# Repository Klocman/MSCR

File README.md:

## MSCR
MSCR is a three-axis DC motor controller for use with robotic arms, for example camera cranes. It can work with any potentiometer-based joystick, and can record and replay movements. This project contains the board layout and firmware. 

## Compiling / Software required
Boards and schematics were created with Eagle PCB v6.6.0. 

Firmare can be opened and compiled with Atmel Studio 6 or newer.

## Photos of the finished controller
[You can view the full gallery here](https://github.com/Klocman/MSCR/tree/master/Documentation/Photos)

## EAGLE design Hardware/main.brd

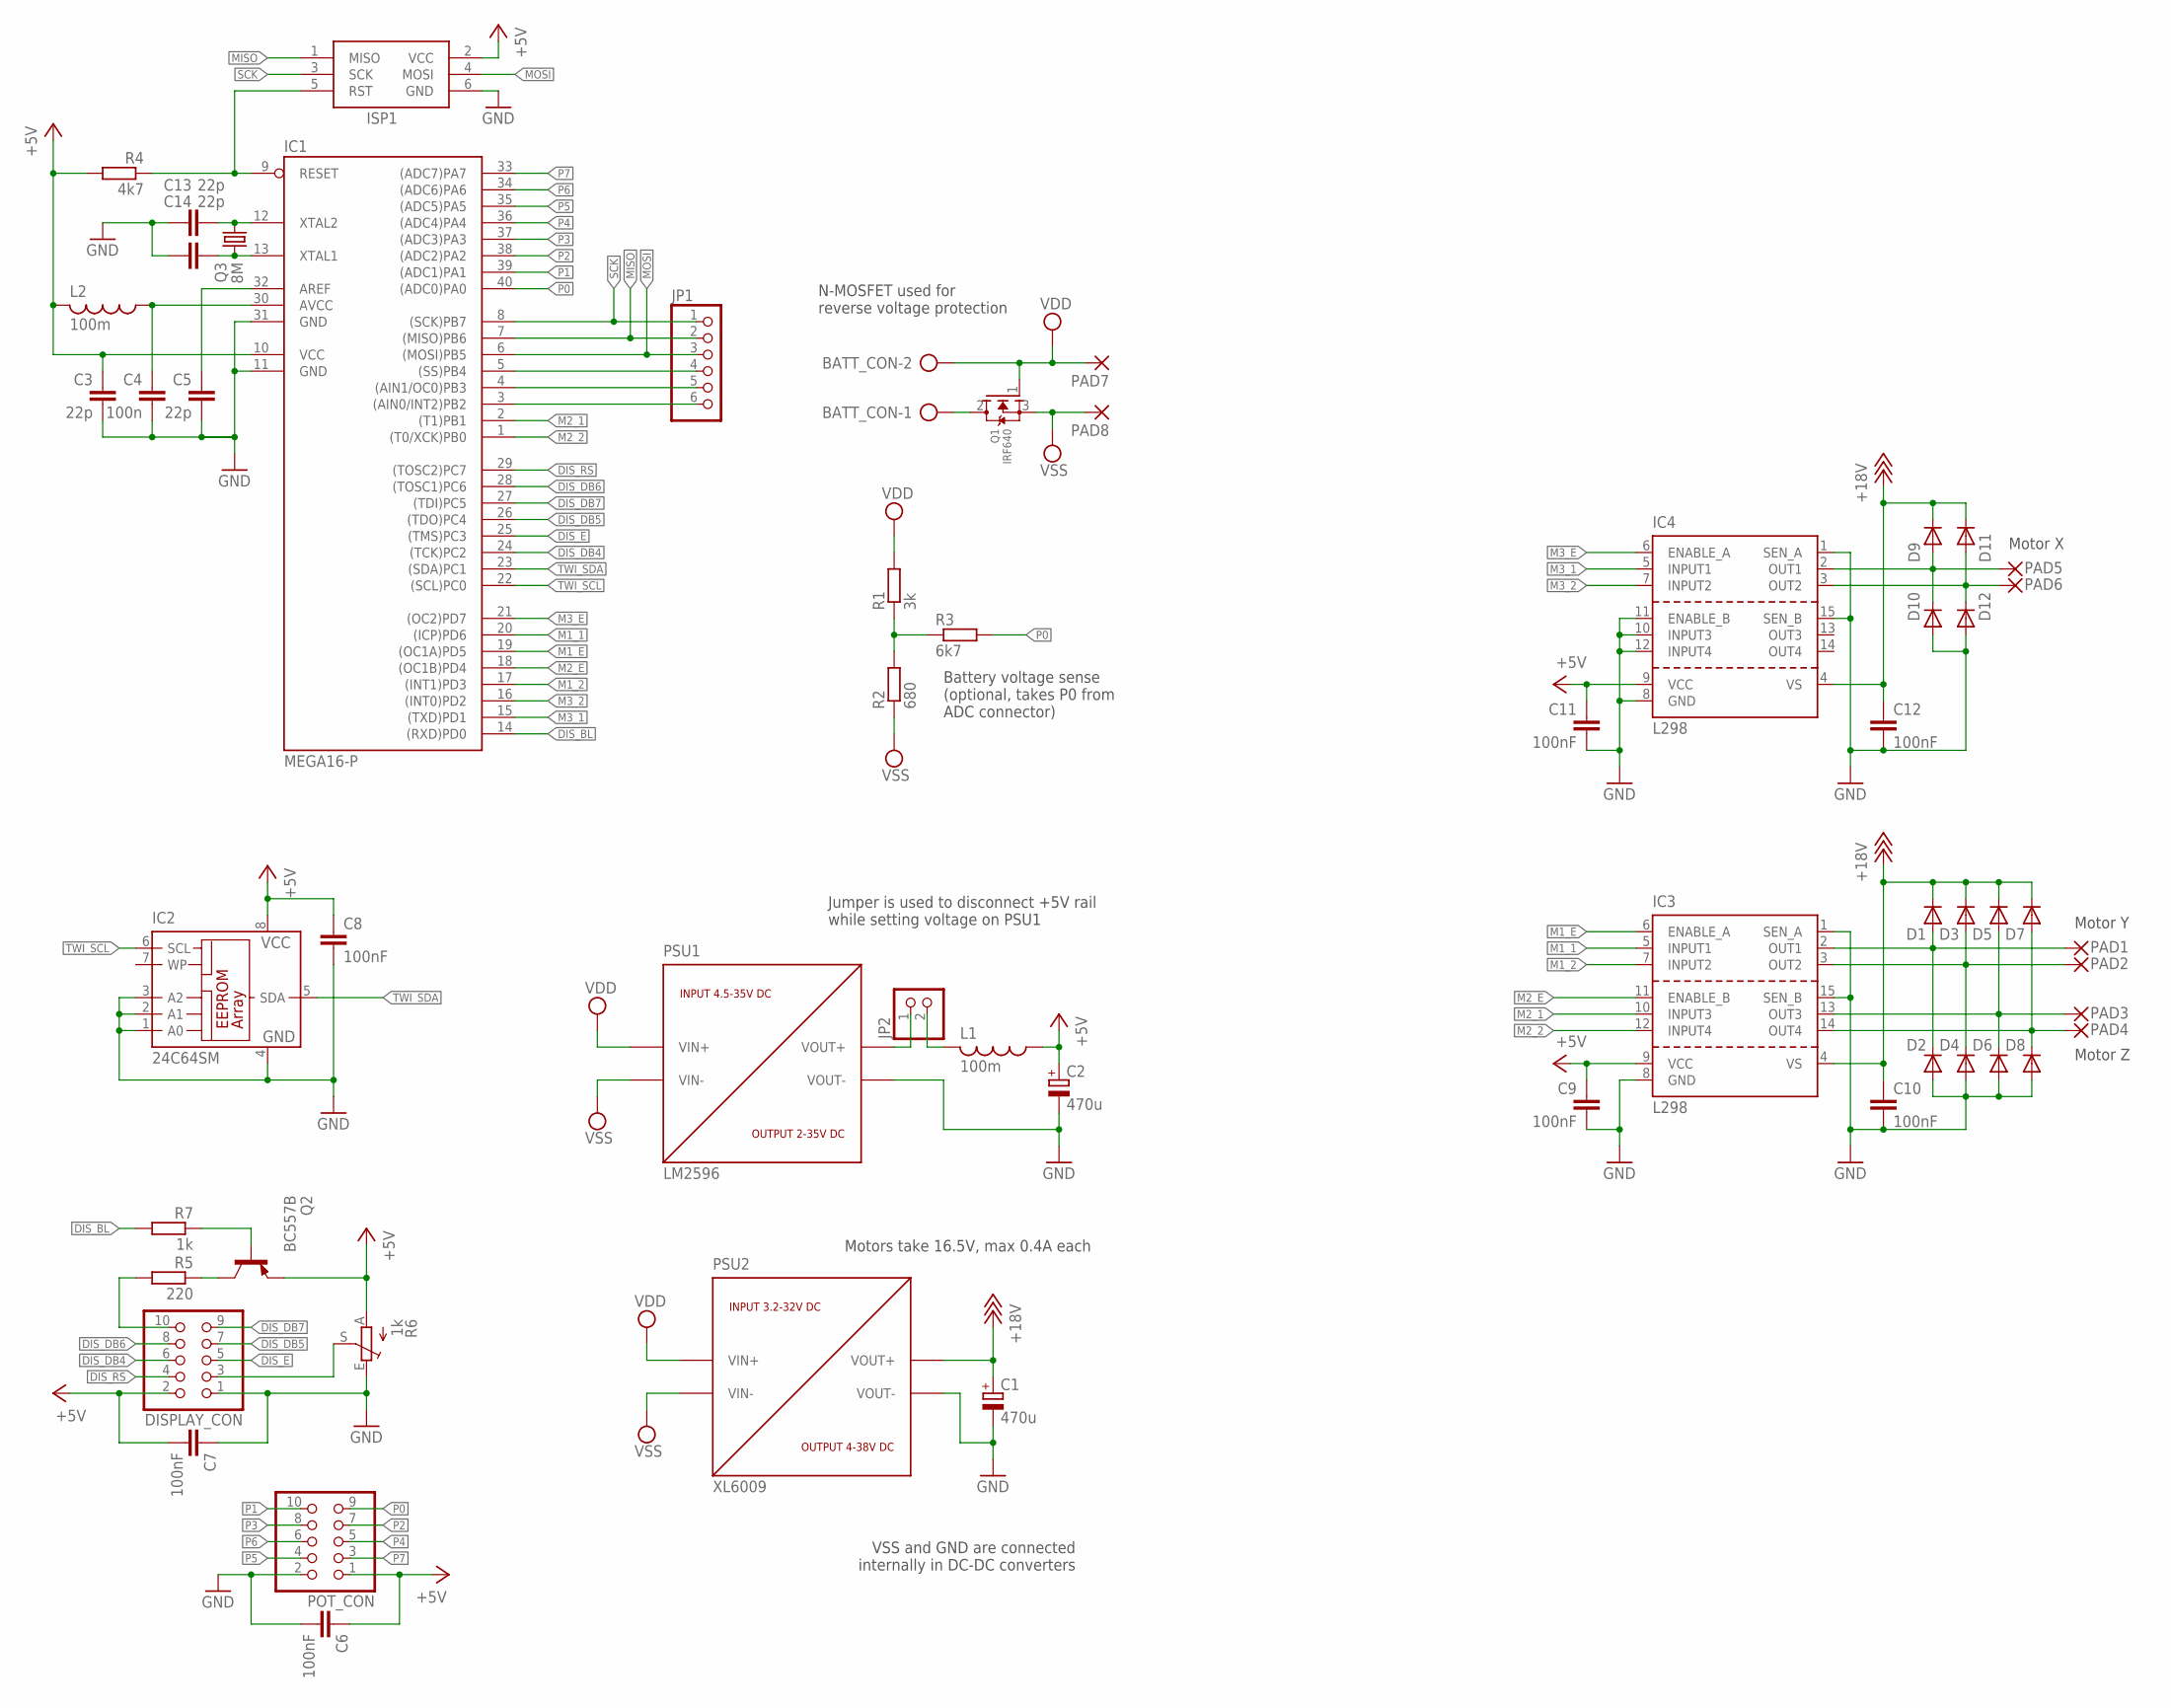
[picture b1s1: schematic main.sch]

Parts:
BATT_CON: AK500/2-H
C1: 470u; E3,5-8
C2: 470u; E5-8,5
C3, C5, C13, C14: 22p; C025-025X050
C4: 100n; C025-025X050
C6: 100nF; C025-025X050
C7, C8: 100nF; C050-024X044
C9, C10, C11, C12: 100nF; C075-032X103
D1, D2, D3, D4, D5, D6, D7, D8, D9, D10, D11, D12: UF4003; DO41-10
DISPLAY_CON: PINHD-2X5; 2X05
IC1: MEGA16-P; DIL40
IC2: 24C64SM; SO-08M
IC3, IC4: L298; MULTIWATT-15
ISP1: AVRISP-6; AVRISP
JP1: PINHD-1X6; 1X06
JP2: PINHD-1X2; 1X02
L1, L2: 100m; 0204/7
PAD1, PAD2, PAD3, PAD4, PAD5, PAD6, PAD7, PAD8: 2,54/1,1KLOCWIRE1; KLOCWIRE1
POT_CON: PINHD-2X5; 2X05
PSU1: LM2596; DC-DC_CONV_MODULE
PSU2: XL6009; DC-DC_CONV_MODULE
Q1: IRF640; TO220V
Q2: BC557B; TO92-EBC
Q3: 8M; TC26V
R1: 3k; 0204/7
R2: 680; 0204/7
R3: 6k7; 0204/5
R4: 4k7; 0204/5
R5: 220; 0204/7
R6: 1k; CA6V
R7: 1k; 0204/7

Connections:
+5V: C2.+, C3.1, C6.1, C7.2, C8.1, C9.1, C11.1, DISPLAY_CON.2, IC1.10 (VCC), IC2.8 (VCC), IC3.9 (VCC), IC4.9 (VCC), ISP1.2 (VCC), L1.1, L2.2, POT_CON.1, Q2.E, R4.2, R6.A
+18V: C1.+, C10.1, C12.1, D1.C, D3.C, D5.C, D7.C, D9.C, D11.C, IC3.4 (VS), IC4.4 (VS), PSU2.OUT+ (VOUT+)
DIS_BL: IC1.14 ((RXD)PD0), R7.2
DIS_DB4: DISPLAY_CON.6, IC1.24 ((TCK)PC2)
DIS_DB5: DISPLAY_CON.7, IC1.26 ((TDO)PC4)
DIS_DB6: DISPLAY_CON.8, IC1.28 ((TOSC1)PC6)
DIS_DB7: DISPLAY_CON.9, IC1.27 ((TDI)PC5)
DIS_E: DISPLAY_CON.5, IC1.25 ((TMS)PC3)
DIS_RS: DISPLAY_CON.4, IC1.29 ((TOSC2)PC7)
DIS_VO: DISPLAY_CON.3, R6.S
GND: C1.-, C2.-, C3.2, C4.2, C5.2, C6.2, C7.1, C8.2, C9.2, C10.2, C11.2, C12.2, C13.2, C14.2, D2.A, D4.A, D6.A, D8.A, D10.A, D12.A, DISPLAY_CON.1, IC1.11 (GND), IC1.31 (GND), IC2.1 (A0), IC2.2 (A1), IC2.3 (A2), IC2.4 (GND), IC3.1 (SEN_A), IC3.8 (GND), IC3.15 (SEN_B), IC4.1 (SEN_A), IC4.8 (GND), IC4.10 (INPUT3), IC4.11 (ENABLE_B), IC4.12 (INPUT4), IC4.15 (SEN_B), ISP1.6 (GND), POT_CON.2, PSU1.OUT- (VOUT-), PSU2.OUT- (VOUT-), R6.E
M1_1: IC1.20 ((ICP)PD6), IC3.5 (INPUT1)
M1_2: IC1.17 ((INT1)PD3), IC3.7 (INPUT2)
M1_E: IC1.19 ((OC1A)PD5), IC3.6 (ENABLE_A)
M2_1: IC1.2 ((T1)PB1), IC3.10 (INPUT3)
M2_2: IC1.1 ((T0/XCK)PB0), IC3.12 (INPUT4)
M2_E: IC1.18 ((OC1B)PD4), IC3.11 (ENABLE_B)
M3_1: IC1.15 ((TXD)PD1), IC4.5 (INPUT1)
M3_2: IC1.16 ((INT0)PD2), IC4.7 (INPUT2)
M3_E: IC1.21 ((OC2)PD7), IC4.6 (ENABLE_A)
MISO: IC1.7 ((MISO)PB6), ISP1.1 (MISO), JP1.2
MOSI: IC1.6 ((MOSI)PB5), ISP1.4 (MOSI), JP1.3
unnamed: JP2.1, PSU1.OUT+ (VOUT+)
unnamed: DISPLAY_CON.10, R5.2
unnamed: IC1.5 ((SS)PB4), JP1.4
unnamed: IC1.4 ((AIN1/OC0)PB3), JP1.5
unnamed: IC1.3 ((AIN0/INT2)PB2), JP1.6
unnamed: BATT_CON.1, Q1.2 (D)
unnamed: D1.A, D2.C, IC3.2 (OUT1), PAD1.1
unnamed: D3.A, D4.C, IC3.3 (OUT2), PAD2.1
unnamed: D5.A, D6.C, IC3.13 (OUT3), PAD3.1
unnamed: D9.A, D10.C, IC4.2 (OUT1), PAD5.1
unnamed: D7.A, D8.C, IC3.14 (OUT4), PAD4.1
unnamed: D11.A, D12.C, IC4.3 (OUT2), PAD6.1
unnamed: C13.1, IC1.12 (XTAL2), Q3.2
unnamed: Q2.C, R5.1
unnamed: C14.1, IC1.13 (XTAL1), Q3.1
unnamed: JP2.2, L1.2
unnamed: Q2.B, R7.1
unnamed: C4.1, IC1.30 (AVCC), L2.1
unnamed: C5.1, IC1.32 (AREF)
unnamed: R1.1, R2.2, R3.1
unnamed: IC1.9 (RESET), ISP1.5 (RST), R4.1
P0: IC1.40 ((ADC0)PA0), POT_CON.9, R3.2
P1: IC1.39 ((ADC1)PA1), POT_CON.10
P2: IC1.38 ((ADC2)PA2), POT_CON.7
P3: IC1.37 ((ADC3)PA3), POT_CON.8
P4: IC1.36 ((ADC4)PA4), POT_CON.5
P5: IC1.35 ((ADC5)PA5), POT_CON.4
P6: IC1.34 ((ADC6)PA6), POT_CON.6
P7: IC1.33 ((ADC7)PA7), POT_CON.3
SCK: IC1.8 ((SCK)PB7), ISP1.3 (SCK), JP1.1
TWI_SCL: IC1.22 ((SCL)PC0), IC2.6 (SCL)
TWI_SDA: IC1.23 ((SDA)PC1), IC2.5 (SDA)
VDD: BATT_CON.2, PAD7.1, PSU1.IN+ (VIN+), PSU2.IN+ (VIN+), Q1.1 (G), R1.2
VSS: PAD8.1, PSU1.IN- (VIN-), PSU2.IN- (VIN-), Q1.3 (S), R2.1

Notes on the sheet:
Battery voltage sense (optional, takes P0 from ADC connector)
VSS and GND are connected internally in DC-DC converters
Motors take 16.5V, max 0.4A each
N-MOSFET used for reverse voltage protection
Jumper is used to disconnect +5V rail while setting voltage on PSU1
Motor Y
Motor Z
Motor X

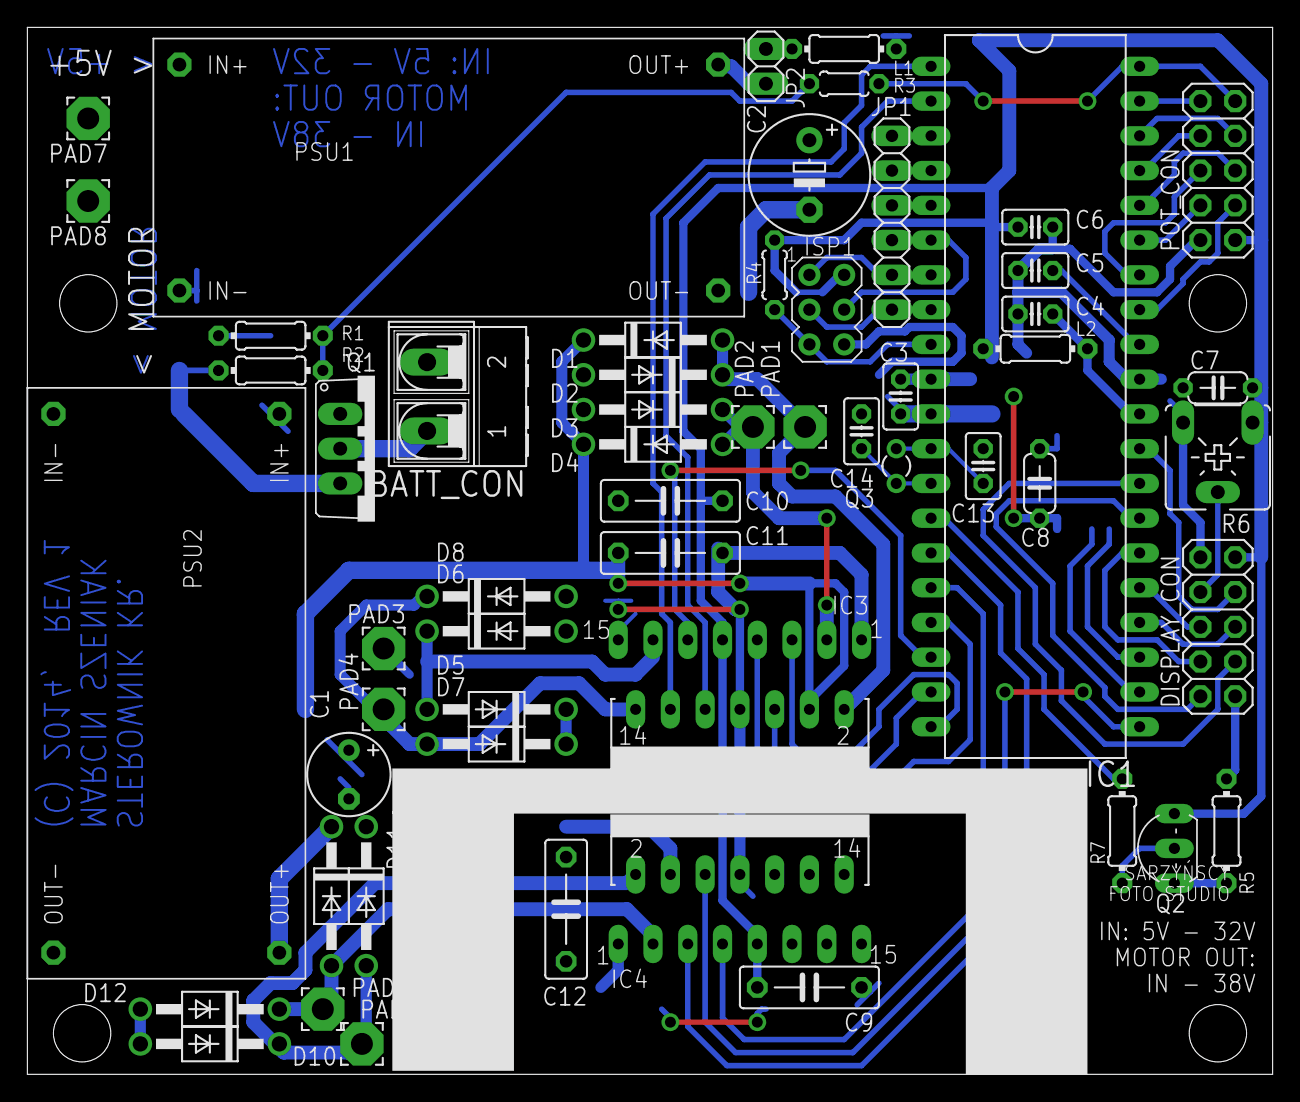
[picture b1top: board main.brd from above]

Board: 2 copper layers, 91.0 x 76.5 mm, 59 parts (1 on the bottom side), 56 nets.

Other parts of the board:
U$1: HEATSINK_GN2611

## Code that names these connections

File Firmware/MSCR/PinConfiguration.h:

/*
*  Copyright 2014 Marcin Szeniak
*/

#ifndef PINCONFIGURATION_H_
#define PINCONFIGURATION_H_

#define M1_1_PIN PIND6
#define M1_2_PIN PIND3
#define M1_12_PORT PORTD
#define M1_12_DDR DDRD
#define M1_E_PIN PIND5
#define M1_E_PORT PORTD
#define M1_E_DDR DDRD
#define M1_E_OCR OCR1AL

#define M2_1_PIN PINB1
#define M2_2_PIN PINB0
#define M2_12_PORT PORTB
#define M2_12_DDR DDRB
#define M2_E_PIN PIND4
#define M2_E_PORT PORTD
#define M2_E_DDR DDRD
#define M2_E_OCR OCR1BL

#define M3_1_PIN PIND1
#define M3_2_PIN PIND2
#define M3_12_PORT PORTD
#define M3_12_DDR DDRD
#define M3_E_PIN PIND7
#define M3_E_PORT PORTD
#define M3_E_DDR DDRD
#define M3_E_OCR OCR2

#define DISPLAY_BL_PIN PIND0
#define DISPLAY_BL_PORT PORTD
#define DISPLAY_BL_DDR DDRD

#define BUTTONS_R1_PIN PINB7
#define BUTTONS_R2_PIN PINB6
#define BUTTONS_R3_PIN PINB5
#define BUTTONS_R4_PIN PINB4
#define BUTTONS_C1_PIN PINB3
#define BUTTONS_C2_PIN PINB2
#define BUTTONS_PORT PORTB
#define BUTTONS_DDR DDRB
#define BUTTONS_PIN PINB

#define AXIS_X_ADC_BIT ADC2_BIT
#define AXIS_Y_ADC_BIT ADC6_BIT
#define AXIS_Z_ADC_BIT ADC3_BIT
#define POT_1_ADC_BIT ADC4_BIT
#define POT_2_ADC_BIT ADc5_BIT
#define POT_3_ADC_BIT ADC7_BIT
#define EXTRA_ADC_BIT ADC1_BIT
#define VBAT_SENSE_ADC_BIT ADC0_BIT

#define AXIS_X_CAL_OFFSET 0
#define AXIS_Y_CAL_OFFSET 1
#define AXIS_Z_CAL_OFFSET 2


#endif /* PINCONFIGURATION_H_ */

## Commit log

2016-10-11 :confetti_ball: Added .gitattributes & .gitignore files
2016-10-11 Moved project to Git

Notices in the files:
Hardware/main.brd:
(C) 2014,  REV 1
